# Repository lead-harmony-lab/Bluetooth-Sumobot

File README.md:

# Bluetooth-Sumobot
Processing code and STL files for the BlueTooth controlled sumobot based on the HC06 module

# Controlling the Sumobot
Download and side-load the [Android app (Arduino Bluetooth Controller)](https://github.com/lead-harmony-lab/Bluetooth-Sumobot/blob/master/Arduino%20bluetooth%20controller_v1.3_apkpure.com.apk) (APK file tested in Android 8.0 on a Samsung S7) - August 2018. 
After installing the app and confirming that your BlueTooth is turned on:
1. Pair with the HC06 module (may be named HC06)
2. Enter password to pair with module (default may be '1234')
3. Launch app.
4. Select module (HC06) from the list of available devices. If not available, confirm step 1.
5. The app will ask which mode to select. Choose 'Controller mode' from top of the list.
6. Confirm solid light on the HC06 module indicating pairing was successful
7. Choose gear/settings icon from top right corner.
8. Configure the field for each icon using these strings. The icon shape is described in the [ ] braces. See [this image](https://github.com/lead-harmony-lab/Bluetooth-Sumobot/blob/master/Arduino%20bluetooth%20controller%20setup%20image.jpg) for a visual guide.
                
                [left arrow] left
                [up arrow] forward
                [right arrow] right
                [down arrow] reverse
                
                [select]
                [start]

                [square] half
                [triangle] faster
                [X] stop
                [circle] slower
REMEMBER: You must select done / checkmark on the keyboard to lock the changes into the app. Otherwise the app will continue to show 'not set' after you have entered in the appropriate text. 

9. Return to the previous screen using the Android back button.
10. Control the sumobot by pressing on the control icons.

# Customizing the Android App
The code for [a basic Android Studio project](https://github.com/lead-harmony-lab/Bluetooth-Sumobot/tree/master/Android%20Sumobot%20Controller/app/src/main) can be modified to add any additional behaviour to the controller that you require. Simply create an new 'Empty Activity' when creating a new project. When the project is loaded, copy over the basic project files into your new project's directory. **REMEMBER** to look up the MAC address of your Bluetooth module and replace the DEVICE ADDRESS in MainActivity.java in order to get this app to work with your Bluetooth module.

# Building the control board
The schematic for controlling this sumbot has been created in KiCad. The gerber files can be sent to a board house (I use [OSHPark](https://oshpark.com)) for fabrication. The schematic can also be used as a basis for putting together a breadboarded version of this project. I've included a hand-drawn image of the pinout I used for the L293D IC when connecting to the Arduino Uno.

# Model File
All of the 3D design work was done in Blender using millimeters. I used Blender 2.79b on Ubuntu 18.04 Linux.

# 3D Printing
I printed these parts out on an FDM RepRap based printer - The Robo3D R1+. Total print time is approximately 24 hours. I recommend that you print the sumobot body on its roof with the motor cavity facing up towards the nozzle. I have found that this model will print successfully without the need to also add support material. I use Matter Control software to control the 3D Printer.

# Arduino Processing Program
Code for this project is complied from a variety of sources from around the Internet. A big shout-out to all the generous people out there that share their code and who make tutorials for other people to follow. I used the Arduino IDE 1.8.5.

# Parts
* Sumobot
  * Tamiya Twin-Motor Gearbox 70097
  * 4-strand data cable
  * Silicon (OooGoo) wheel grips (you will have to design your own hubs)
* BlueTooth Module
  * HC06 Bluetooth Module https://www.ebay.ca/itm/201415076859
  * Single battery (pos & neg) terminals: https://www.ebay.ca/itm/311070764299
  * Battery conversion spring: https://www.ebay.ca/itm/172440758009
  * Latching DPDT switch: https://www.ebay.ca/itm/322498646783
  * Single-row male header pins: https://www.ebay.ca/itm/181918556293
  * Single-row female header socket: https://www.ebay.ca/itm/192600775159
  * 1K axial resistor
  * 2K axial resistor
  * 150R axial resistor
  * 100uf electrolytic capacitor: https://www.ebay.ca/itm/291535579746
  * 0.1uf ceramic capacitor: https://www.ebay.ca/itm/323377133385
  * L293D IC (Quadruple H-Bridge driver with internal fly-back diodes): https://www.ebay.ca/itm/311173671055
  * 16 pin DIP socket: https://www.ebay.ca/itm/311563518356
  * Arduino UNO: https://www.ebay.ca/itm/263452480977
  * Arduino UNO prototype shield: https://www.ebay.ca/itm/172536470483
  * 4 AA Batteries
  * 9V Battery
  * 9 Volt Battery Clip: https://www.ebay.ca/itm/263766384151
  * Hook-up wire: https://www.ebay.ca/itm/372234345012
  * Heat Shrink Tubing: https://www.ebay.ca/itm/381381208587
  * Dupont 4-Pin 2.54mm Housing: https://www.ebay.ca/itm/152837501538
  * Dupont 2-Pin 2.54mm Housing: https://www.ebay.ca/itm/331824268796
  * Dupont Female Connector Terminal: https://www.ebay.ca/itm/141975933772
  * HT-225D Dupont Crimping Tool: https://www.ebay.ca/itm/263766640490
  * M2 x 8mm self-tapping screws: https://www.ebay.ca/itm/182309825046?var=484855861567
  * M3 x 6mm self-tapping screws: https://www.ebay.ca/itm/182309825046?var=484855861608

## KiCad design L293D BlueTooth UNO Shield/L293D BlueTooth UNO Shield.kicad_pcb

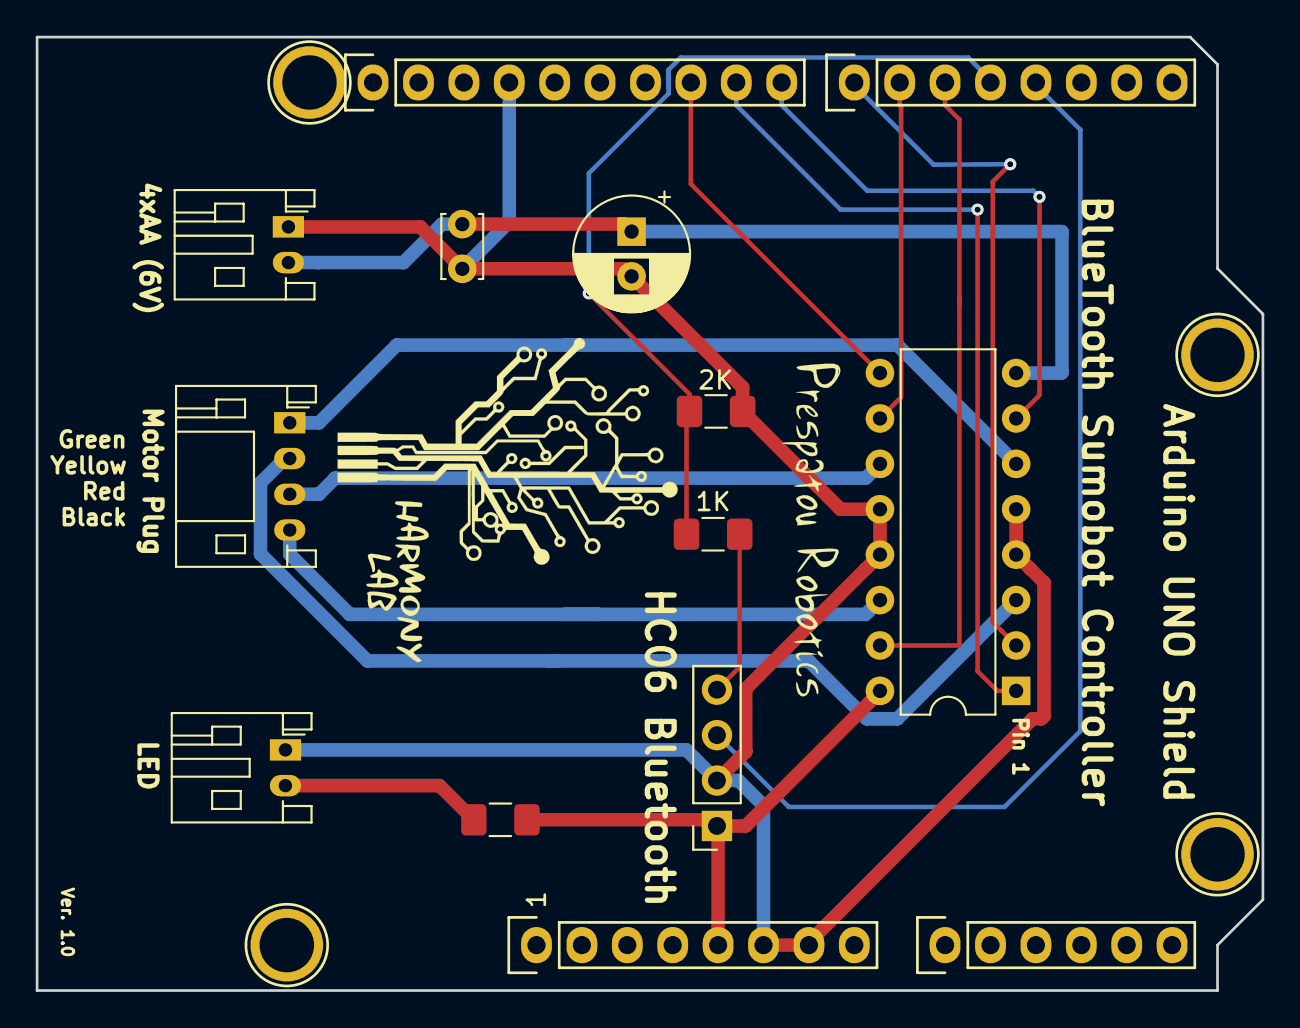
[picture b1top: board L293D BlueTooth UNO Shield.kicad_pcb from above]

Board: 2 copper layers, 68.6 x 53.3 mm, 18 parts (0 on the bottom side), 17 nets.

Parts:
1K: 1K; R_1206_3216Metric_Pad1.42x1.75mm_HandSolder
2K: 2K; R_1206_3216Metric_Pad1.42x1.75mm_HandSolder
150R1: R; R_1206_3216Metric_Pad1.42x1.75mm_HandSolder
C1: 0.1uf; C_Disc_D3.4mm_W2.1mm_P2.50mm
C2: 100uf; CP_Radial_D6.3mm_P2.50mm
D1: LED; JST_PH_S2B-PH-K_1x02_P2.00mm_Horizontal
J1: HC06; PinSocket_1x04_P2.54mm_Vertical
J2: 6V Power (4xAA); JST_PH_S2B-PH-K_1x02_P2.00mm_Horizontal
J3: Motor Connector; JST_PH_S4B-PH-K_1x04_P2.00mm_Horizontal
P1: Power; Socket_Strip_Arduino_1x08
P2: Analog; Socket_Strip_Arduino_1x06
P3: Digital; Socket_Strip_Arduino_1x10
P4: Digital; Socket_Strip_Arduino_1x08
P5, P6, P7, P8: CONN_01X01; Arduino_1pin
U1: L293D; DIP-16_W7.62mm

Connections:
+5V: 150R1.1, J1.1, P1.5, U1.16
+6V: C1.1, C2.1, J2.2, U1.8
/3(**): J1.3, P4.5
/4: 1K.1, 2K.2, P4.4
/5(**): P4.3, U1.15
/6(**): P4.2, U1.10
/7: P4.1, U1.2
/8: P3.10, U1.7
/9(**): P3.9, U1.1
/10(**/SS): P3.8, U1.9
GND: 2K.1, C1.2, C2.2, D1.1, J1.2, J2.1, P1.6, P1.7, P3.4, U1.4, U1.5, U1.12, U1.13
unnamed: 150R1.2, D1.2
unnamed: 1K.2, J1.4
unnamed: J3.1, U1.6
unnamed: J3.2, U1.3
unnamed: J3.3, U1.11
unnamed: J3.4, U1.14

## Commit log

2018-08-22 Create README.md
    Created new repository
2018-08-22 Create LICENSE
    Attached license.
2018-08-22 Update .gitignore
    Ignore for Processing projects
2018-08-22 Add files via upload
    Code for the Bluetooth sumobot using the HC06 module on Arduino UNO
2018-08-22 Android BlueTooth Controller App
    App used for controlling the sumobot. Must be side loaded as the app no longer exists on the Play store.
2018-08-22 Update README.md
    Instructions on how to control the sumobot using the apk file on Android.
2018-08-22 Update README.md
    Correction
2018-08-22 Add files via upload
    Images of project
2018-08-22 KiCad project files
    Sumobot control board schematic and KiCad files
2018-08-22 Add files via upload
    Hand-drawn pinout
2018-08-22 Delete 20180821_203618.jpg
    Redundant
2018-08-22 Add files via upload
    3D model files of the BlueTooth sumobot
2018-08-22 Update README.md
    Update BOM
2018-08-22 Update README.md
    Updates to BOM
2018-08-22 Update README.md
    Updated BOM
2018-08-22 Update README.md
    Added sections on Blender and Processing
2018-08-22 Screenshot of configuringing BT app
    Screenshot of how to configure the Arduino BlueTooth Controller app.
2018-08-22 Update README.md
    Added image link
2018-08-22 Update README.md
    Changed image link to use markdown
2018-08-22 Update README.md
    Correct spacing
2018-08-22 Update README.md
    Fix markdown
2018-08-22 Update README.md
    Fix spacing
2018-08-22 Update README.md
    OSHPark link
2018-08-22 Update README.md
    Punctuation
2018-08-22 Update README.md
    clarifications
2018-08-22 Update README.md
    Move image link
2018-08-22 Update README.md
    Corrections
2018-08-22 Add files via upload
    Added wheel hub
2018-08-22 Android Studio code for cutom controller
    SRC folder from an Android Studio project to create a custom BlueTooth controller. Create an empty activity in Android Studio and copy the contents of the src folder into the project directory. REMEM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
2018-08-22 Update README.md
    Added link
2018-08-22 Update README.md
    Added description of the Android App code files.
2018-08-22 Add files via upload
    Board Renderings
